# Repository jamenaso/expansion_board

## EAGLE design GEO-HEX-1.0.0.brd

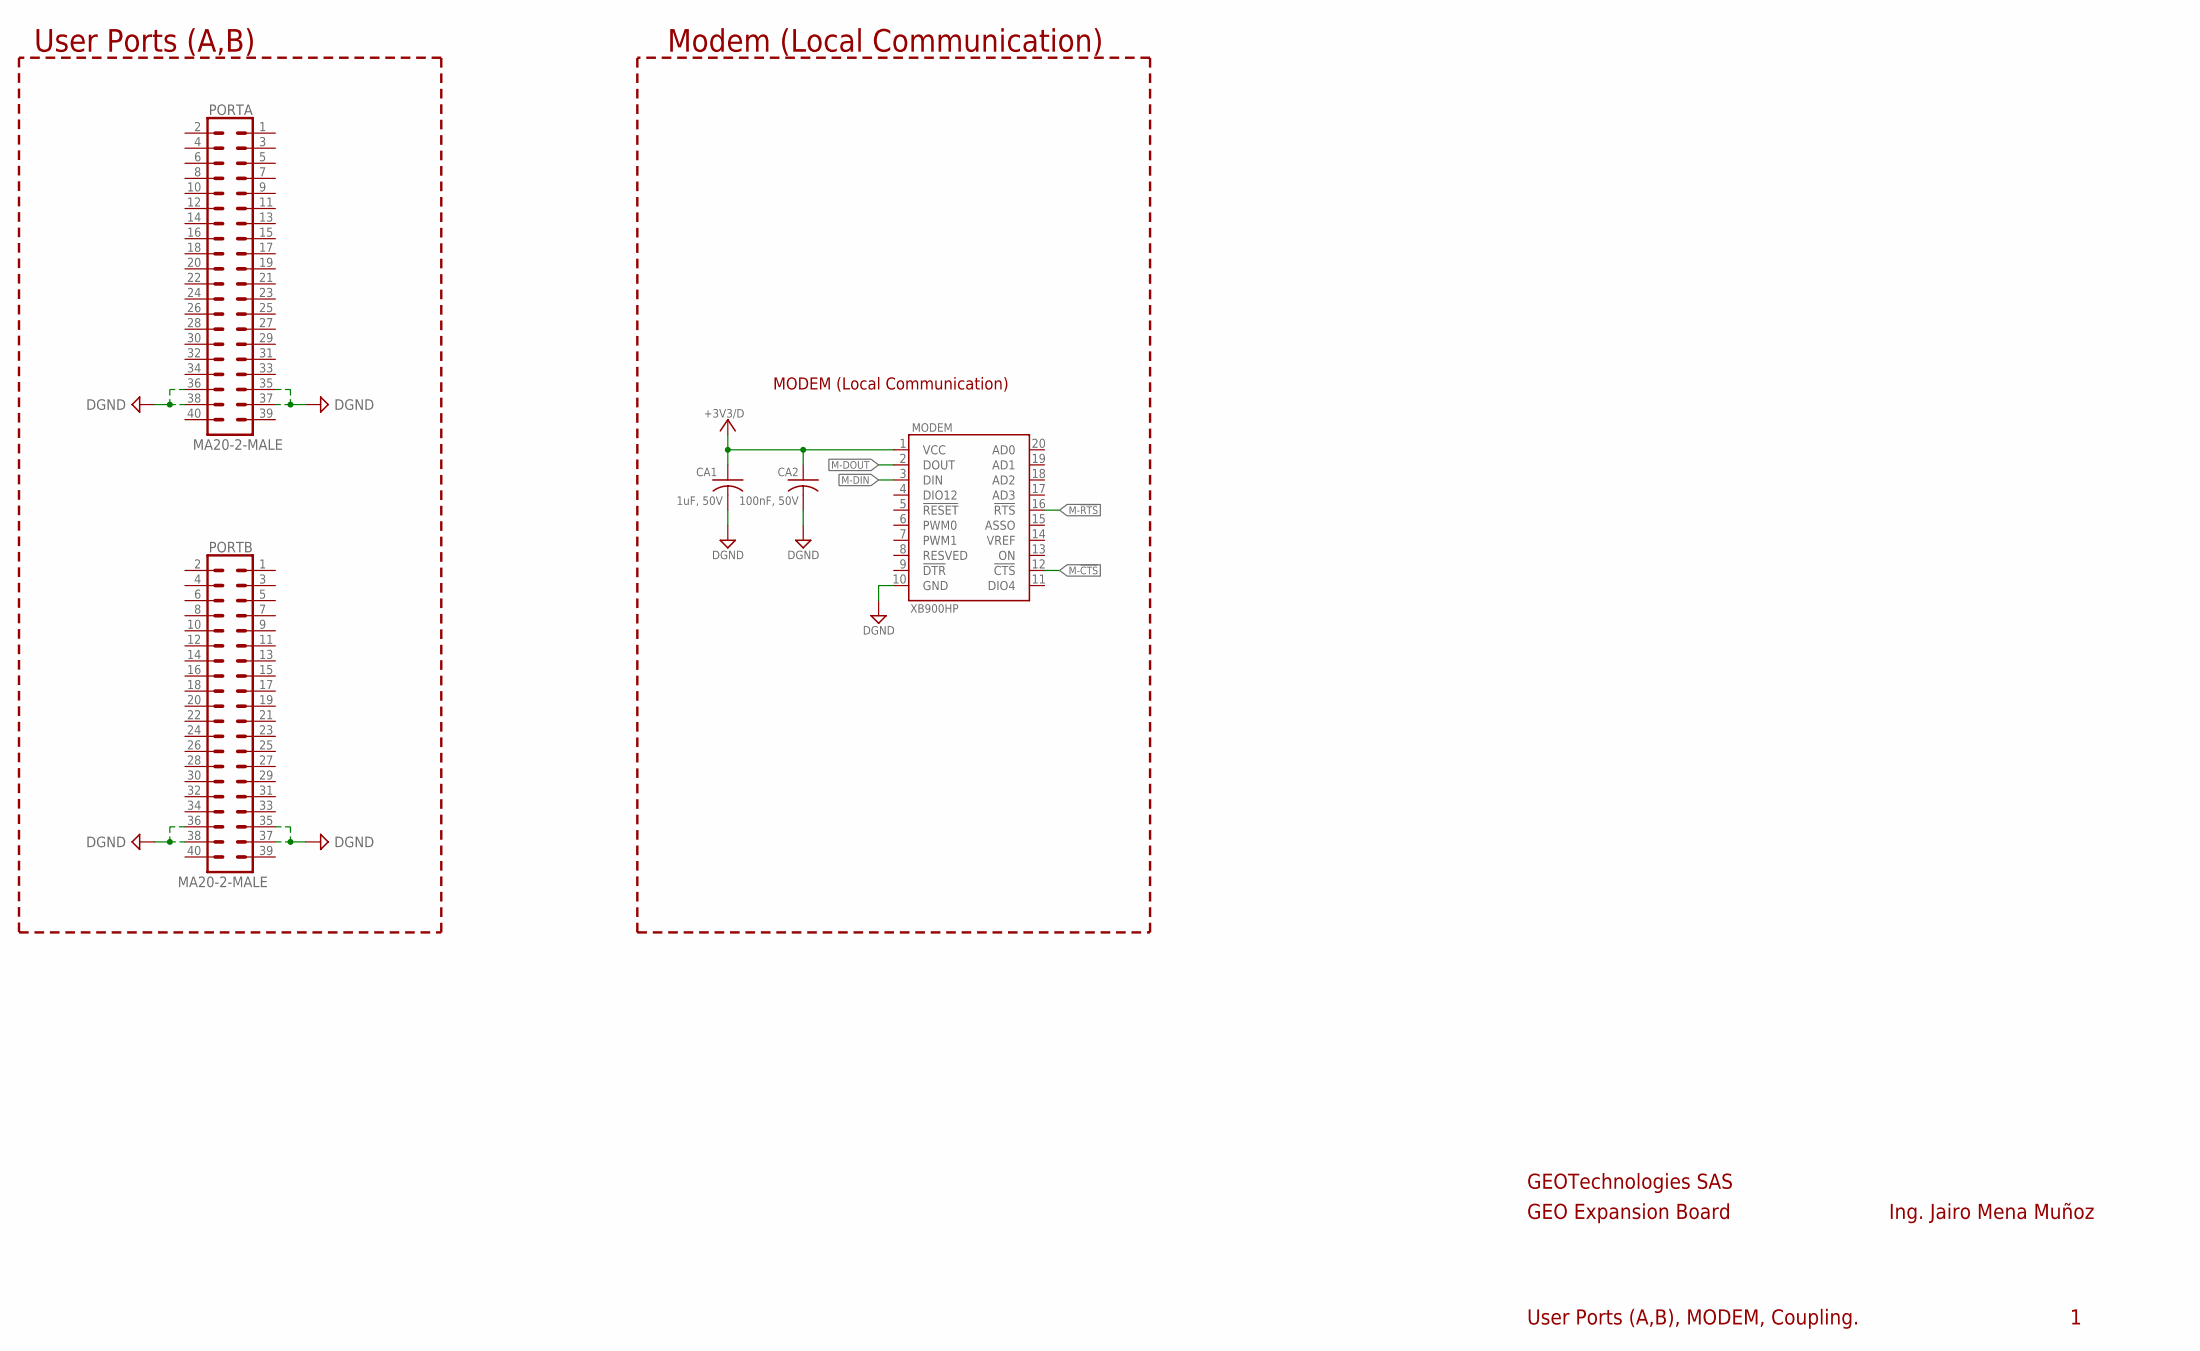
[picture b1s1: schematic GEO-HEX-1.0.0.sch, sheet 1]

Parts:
CA1: 1uF, 50V; C0805
CA2: 100nF, 50V; C0805
MODEM: XB900HP; XBEEPRO
PORTA: MA20-2-MALE
PORTB: MA20-2-MALE

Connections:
+3V3/D: CA1.1, CA2.1, MODEM.1 (VCC); also elsewhere on the board
DGND: CA1.2, CA2.2, MODEM.10 (GND), PORTA.35, PORTA.36, PORTA.37, PORTA.38, PORTB.35, PORTB.36, PORTB.37, PORTB.38
M-!CTS: MODEM.12 (!CTS)
M-!RTS: MODEM.16 (!RTS)
M-DIN: MODEM.3 (DIN)
M-DOUT: MODEM.2 (DOUT)

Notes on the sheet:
GEOTechnologies SAS
GEO Expansion Board
Ing. Jairo Mena Muñoz
User Ports (A,B), MODEM, Coupling.
User Ports (A,B)
MODEM (Local Communication)
Modem (Local Communication)

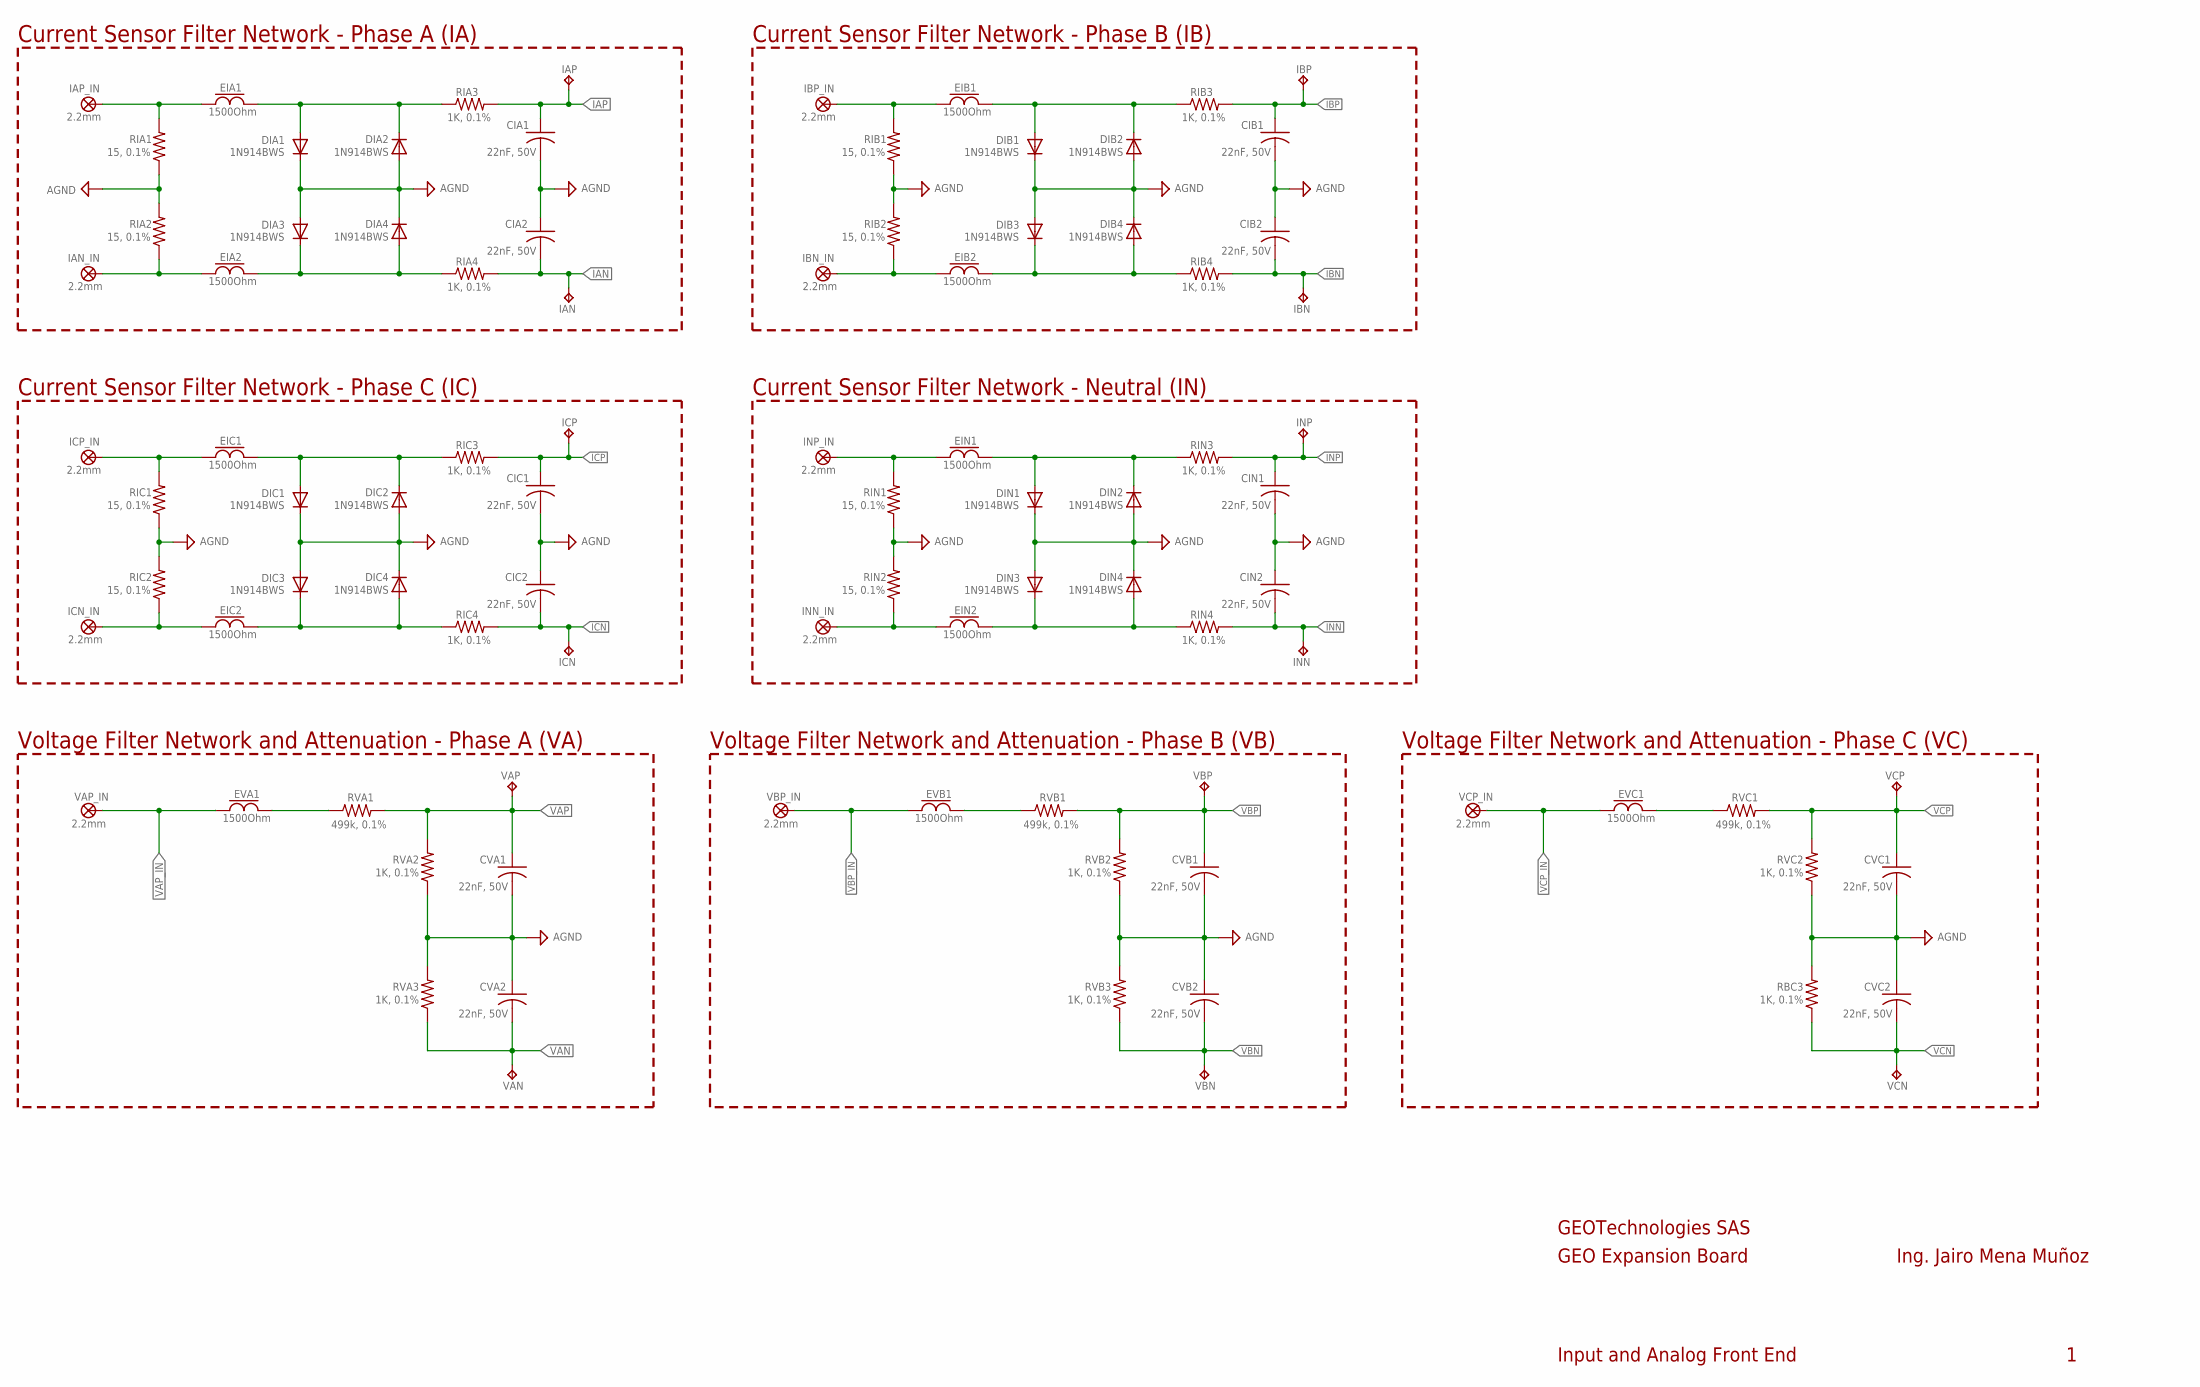
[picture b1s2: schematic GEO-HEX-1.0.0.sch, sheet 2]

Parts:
CIA1, CIA2: 22nF, 50V; C0805
CIB1, CIB2: 22nF, 50V; C0805
CIC1, CIC2: 22nF, 50V; C0805
CIN1, CIN2: 22nF, 50V; C0805
CVA1, CVA2: 22nF, 50V; C0805
CVB1, CVB2: 22nF, 50V; C0805
CVC1, CVC2: 22nF, 50V; C0805
DIA1, DIA2, DIA3, DIA4: 1N914BWS; SOD-323FL
DIB1, DIB2, DIB3, DIB4: 1N914BWS; SOD-323FL
DIC1, DIC2, DIC3, DIC4: 1N914BWS; SOD-323FL
DIN1, DIN2, DIN3, DIN4: 1N914BWS; SOD-323FL
EIA1, EIA2: 1500Ohm; L0805
EIB1, EIB2: 1500Ohm; L0805
EIC1, EIC2: 1500Ohm; L0805
EIN1, EIN2: 1500Ohm; L0805
EVA1: 1500Ohm; L0805
EVB1: 1500Ohm; L0805
EVC1: 1500Ohm; L0805
IAN: TPPAD1-13; P1-10
IAN_IN: 2.2mm; TURRET
IAP: TPPAD1-13; P1-10
IAP_IN: 2.2mm; TURRET
IBN: TPPAD1-13; P1-10
IBN_IN: 2.2mm; TURRET
IBP: TPPAD1-13; P1-10
IBP_IN: 2.2mm; TURRET
ICN: TPPAD1-13; P1-10
ICN_IN: 2.2mm; TURRET
ICP: TPPAD1-13; P1-10
ICP_IN: 2.2mm; TURRET
INN: TPPAD1-13; P1-10
INN_IN: 2.2mm; TURRET
INP: TPPAD1-13; P1-10
INP_IN: 2.2mm; TURRET
RBC3: 1K, 0.1%; R0805
RIA1, RIA2: 15, 0.1%; R0805
RIA3, RIA4: 1K, 0.1%; R0805
RIB1, RIB2: 15, 0.1%; R0805
RIB3, RIB4: 1K, 0.1%; R0805
RIC1, RIC2: 15, 0.1%; R0805
RIC3, RIC4: 1K, 0.1%; R0805
RIN1, RIN2: 15, 0.1%; R0805
RIN3, RIN4: 1K, 0.1%; R0805
RVA1: 499k, 0.1%; R1206
RVA2, RVA3: 1K, 0.1%; R0805
RVB1: 499k, 0.1%; R1206
RVB2, RVB3: 1K, 0.1%; R0805
RVC1: 499k, 0.1%; R1206
RVC2: 1K, 0.1%; R0805
VAN: TPPAD1-13; P1-10
VAP: TPPAD1-13; P1-10
VAP_IN: 2.2mm; TURRET
VBN: TPPAD1-13; P1-10
VBP: TPPAD1-13; P1-10
VBP_IN: 2.2mm; TURRET
VCN: TPPAD1-13; P1-10
VCP: TPPAD1-13; P1-10
VCP_IN: 2.2mm; TURRET

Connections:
AGND: CIA1.2, CIA2.1, CIB1.2, CIB2.1, CIC1.2, CIC2.1, CIN1.2, CIN2.1, CVA1.2, CVA2.1, CVB1.2, CVB2.1, CVC1.2, CVC2.1, DIA1.C, DIA2.A, DIA3.A, DIA4.C, DIB1.C, DIB2.A, DIB3.A, DIB4.C, DIC1.C, DIC2.A, DIC3.A, DIC4.C, DIN1.C, DIN2.A, DIN3.A, DIN4.C, RBC3.2, RIA1.1, RIA2.2, RIB1.1, RIB2.2, RIC1.1, RIC2.2, RIN1.1, RIN2.2, RVA2.1, RVA3.2, RVB2.1, RVB3.2, RVC2.1; also elsewhere on the board
IAN: CIA2.2, IAN.TP, RIA4.2; also elsewhere on the board
IAP: CIA1.1, IAP.TP, RIA3.2; also elsewhere on the board
IBN: CIB2.2, IBN.TP, RIB4.2; also elsewhere on the board
IBP: CIB1.1, IBP.TP, RIB3.2; also elsewhere on the board
ICN: CIC2.2, ICN.TP, RIC4.2; also elsewhere on the board
ICP: CIC1.1, ICP.TP, RIC3.2; also elsewhere on the board
INN: CIN2.2, INN.TP, RIN4.2; also elsewhere on the board
INP: CIN1.1, INP.TP, RIN3.2; also elsewhere on the board
unnamed: EVA1.2, RVA1.1
unnamed: EIA1.1, IAP_IN.P1, RIA1.2
unnamed: EIA2.1, IAN_IN.P1, RIA2.1
unnamed: DIA1.A, DIA2.C, EIA1.2, RIA3.1
unnamed: DIA3.C, DIA4.A, EIA2.2, RIA4.1
unnamed: EIB1.1, IBP_IN.P1, RIB1.2
unnamed: EIB2.1, IBN_IN.P1, RIB2.1
unnamed: DIB1.A, DIB2.C, EIB1.2, RIB3.1
unnamed: DIB3.C, DIB4.A, EIB2.2, RIB4.1
unnamed: EIC1.1, ICP_IN.P1, RIC1.2
unnamed: EIC2.1, ICN_IN.P1, RIC2.1
unnamed: DIC1.A, DIC2.C, EIC1.2, RIC3.1
unnamed: DIC3.C, DIC4.A, EIC2.2, RIC4.1
unnamed: EVB1.2, RVB1.1
unnamed: EVC1.2, RVC1.1
unnamed: EIN1.1, INP_IN.P1, RIN1.2
unnamed: EIN2.1, INN_IN.P1, RIN2.1
unnamed: DIN1.A, DIN2.C, EIN1.2, RIN3.1
unnamed: DIN3.C, DIN4.A, EIN2.2, RIN4.1
VAN: CVA2.2, RVA3.1, VAN.TP; also elsewhere on the board
VAP: CVA1.1, RVA1.2, RVA2.2, VAP.TP; also elsewhere on the board
VAP_IN: EVA1.1, VAP_IN.P1
VBN: CVB2.2, RVB3.1, VBN.TP; also elsewhere on the board
VBP: CVB1.1, RVB1.2, RVB2.2, VBP.TP; also elsewhere on the board
VBP_IN: EVB1.1, VBP_IN.P1
VCN: CVC2.2, RBC3.1, VCN.TP; also elsewhere on the board
VCP: CVC1.1, RVC1.2, RVC2.2, VCP.TP; also elsewhere on the board
VCP_IN: EVC1.1, VCP_IN.P1

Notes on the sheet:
GEOTechnologies SAS
GEO Expansion Board
Ing. Jairo Mena Muñoz
Input and Analog Front End
Current Sensor Filter Network - Phase A (IA)
Voltage Filter Network and Attenuation - Phase A (VA)
Current Sensor Filter Network - Neutral (IN)
Current Sensor Filter Network - Phase B (IB)
Current Sensor Filter Network - Phase C (IC)
Voltage Filter Network and Attenuation - Phase B (VB)
Voltage Filter Network and Attenuation - Phase C (VC)

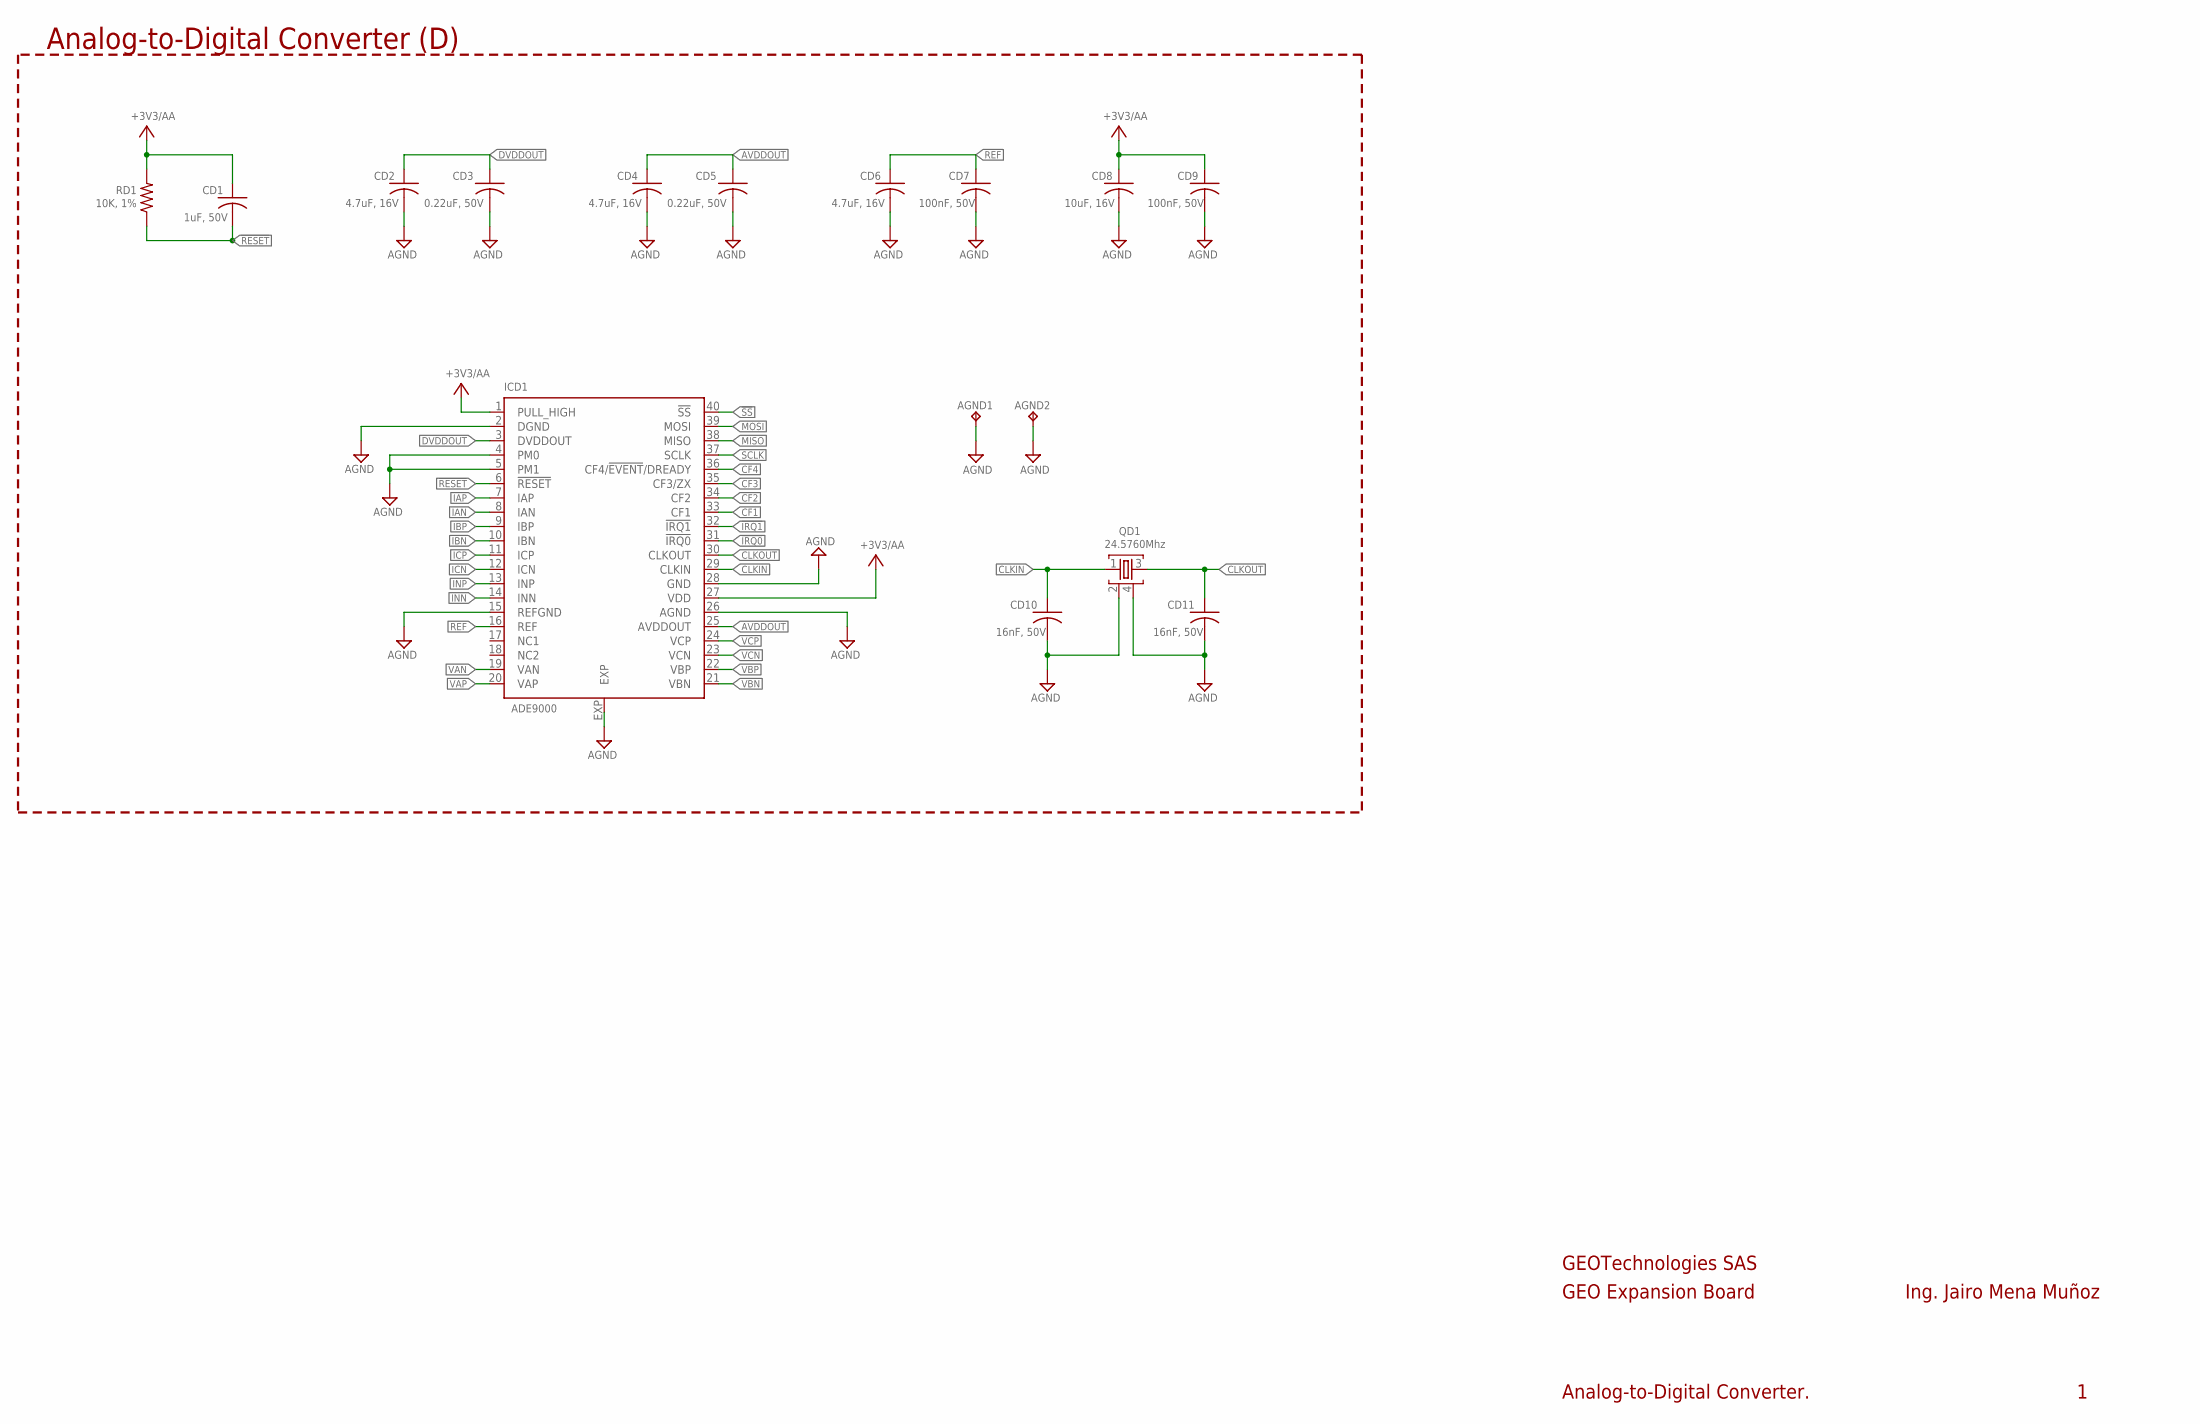
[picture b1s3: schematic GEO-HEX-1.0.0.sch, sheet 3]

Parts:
AGND1, AGND2: TPPAD1-13; P1-10
CD1: 1uF, 50V; C0805
CD2, CD4, CD6: 4.7uF, 16V; C0805
CD3, CD5: 0.22uF, 50V; C0805
CD7, CD9: 100nF, 50V; C0805
CD8: 10uF, 16V; C0805
CD10, CD11: 16nF, 50V; C0805
ICD1: ADE9000; LFCSP40
QD1: 24.5760Mhz; 4-SMD
RD1: 10K, 1%; R0805

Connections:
!IRQ0: ICD1.31 (!IRQ0)
!IRQ1: ICD1.32 (!IRQ1)
!RESET: CD1.2, ICD1.6 (!RESET), RD1.1
!SS: ICD1.40 (!SS)
+3V3/AA: CD1.1, CD8.1, CD9.1, ICD1.1 (PULL_HIGH), ICD1.27 (VDD), RD1.2; also elsewhere on the board
AGND: AGND1.TP, AGND2.TP, CD2.2, CD3.2, CD4.2, CD5.2, CD6.2, CD7.2, CD8.2, CD9.2, CD10.2, CD11.2, ICD1.2 (DGND), ICD1.4 (PM0), ICD1.5 (PM1), ICD1.15 (REFGND), ICD1.26 (AGND), ICD1.28 (GND), ICD1.EXP, QD1.2, QD1.4; also elsewhere on the board
AVDDOUT: CD4.1, CD5.1, ICD1.25 (AVDDOUT)
CF1: ICD1.33 (CF1)
CF2: ICD1.34 (CF2)
CF3: ICD1.35 (CF3/ZX)
CF4: ICD1.36 (CF4/!EVENT!/DREADY)
CLKIN: CD10.1, ICD1.29 (CLKIN), QD1.1
CLKOUT: CD11.1, ICD1.30 (CLKOUT), QD1.3
DVDDOUT: CD2.1, CD3.1, ICD1.3 (DVDDOUT)
IAN: ICD1.8 (IAN); also elsewhere on the board
IAP: ICD1.7 (IAP); also elsewhere on the board
IBN: ICD1.10 (IBN); also elsewhere on the board
IBP: ICD1.9 (IBP); also elsewhere on the board
ICN: ICD1.12 (ICN); also elsewhere on the board
ICP: ICD1.11 (ICP); also elsewhere on the board
INN: ICD1.14 (INN); also elsewhere on the board
INP: ICD1.13 (INP); also elsewhere on the board
MISO: ICD1.38 (MISO)
MOSI: ICD1.39 (MOSI)
REF: CD6.1, CD7.1, ICD1.16 (REF)
SCLK: ICD1.37 (SCLK)
VAN: ICD1.19 (VAN); also elsewhere on the board
VAP: ICD1.20 (VAP); also elsewhere on the board
VBN: ICD1.21 (VBN); also elsewhere on the board
VBP: ICD1.22 (VBP); also elsewhere on the board
VCN: ICD1.23 (VCN); also elsewhere on the board
VCP: ICD1.24 (VCP); also elsewhere on the board

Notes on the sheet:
GEOTechnologies SAS
GEO Expansion Board
Ing. Jairo Mena Muñoz
Analog-to-Digital Converter.
Analog-to-Digital Converter (D)

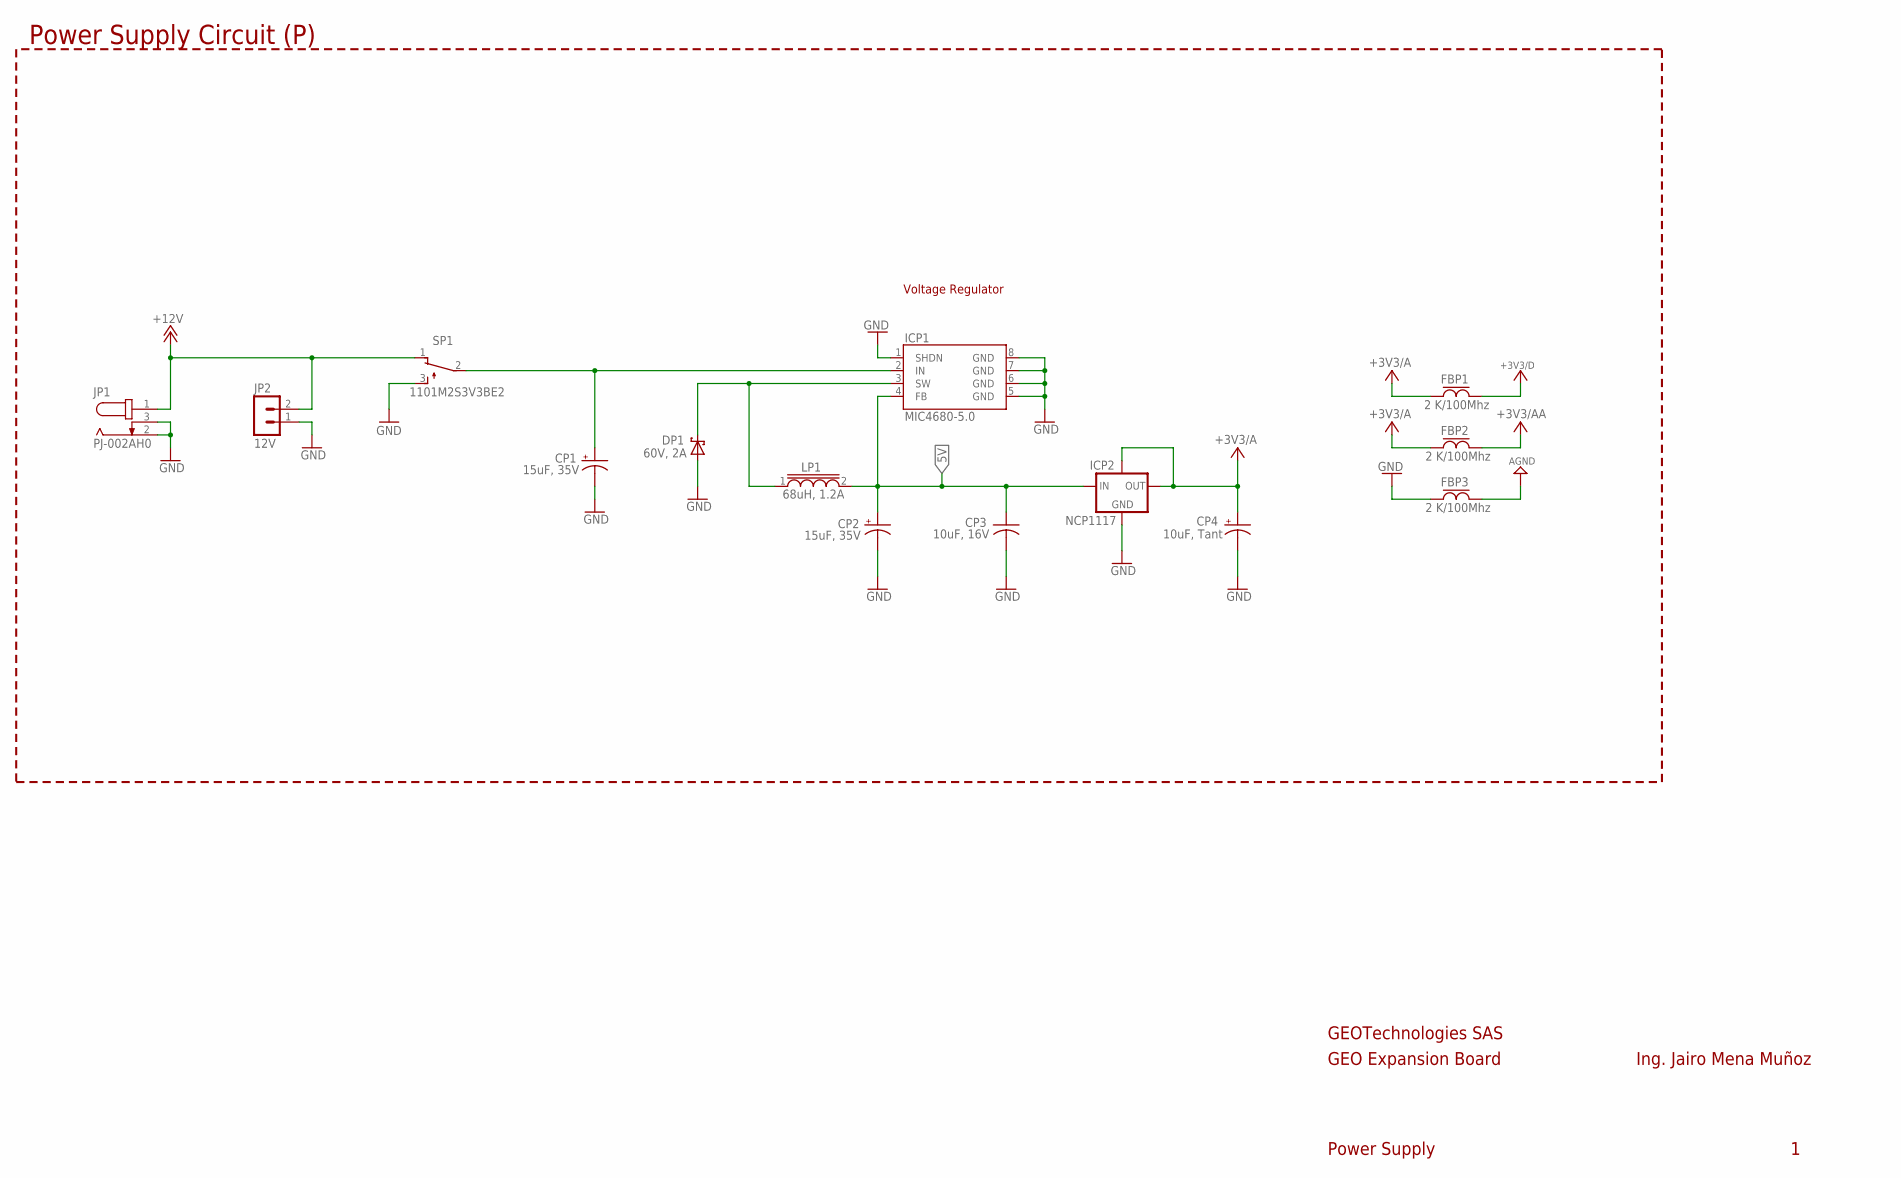
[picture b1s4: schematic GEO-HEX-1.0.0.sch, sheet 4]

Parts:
CP1, CP2: 15uF, 35V; SMC_D
CP3: 10uF, 16V; C0805
CP4: 10uF, Tant; SMC_P
DP1: 60V, 2A; 2-SMD
FBP1, FBP2, FBP3: 2 K/100Mhz; L1210
ICP1: MIC4680-5.0; SO8
ICP2: NCP1117; SOT223
JP1: PJ-002AH0; JACK
JP2: 12V; PW2
LP1: 68uH, 1.2A; DR7X7
SP1: 1101M2S3V3BE2

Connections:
5V: CP2.+, CP3.1, ICP1.4 (FB), ICP2.3 (IN), LP1.2
+3V3/A: CP4.+, FBP1.1, FBP2.1, ICP2.2 (OUT), ICP2.4 (TAB)
+3V3/AA: FBP2.2; also elsewhere on the board
+3V3/D: FBP1.2; also elsewhere on the board
+12V: JP1.1, JP2.2, SP1.1
AGND: FBP3.2; also elsewhere on the board
GND: CP1.-, CP2.-, CP3.2, CP4.-, DP1.A, FBP3.1, ICP1.1 (SHDN), ICP1.5 (GND), ICP1.6 (GND), ICP1.7 (GND), ICP1.8 (GND), ICP2.1 (AGND), JP1.2, JP1.3, JP2.1, SP1.3
unnamed: CP1.+, ICP1.2 (IN), SP1.2
SW: DP1.C, ICP1.3 (SW), LP1.1

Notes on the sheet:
GEOTechnologies SAS
GEO Expansion Board
Ing. Jairo Mena Muñoz
Power Supply
Power Supply Circuit (P)
Voltage Regulator

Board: 2 copper layers, 126 parts (14 on the bottom side), 52 nets, no tracks yet.

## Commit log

2020-09-16 Primera versión del Esquemático e Inicio en Board
    Se implementa primera versión del Esquemático, se implementa las medidas en board y se emepiza con la organización de elementos en Board.
2020-09-24 Se organizan elementos en el Board
    Se implementa toda la organización de los elementos en board. Falta incluir los opto-acopladores de comunicación entre el ADE9000 y el puerto de de E/S.
